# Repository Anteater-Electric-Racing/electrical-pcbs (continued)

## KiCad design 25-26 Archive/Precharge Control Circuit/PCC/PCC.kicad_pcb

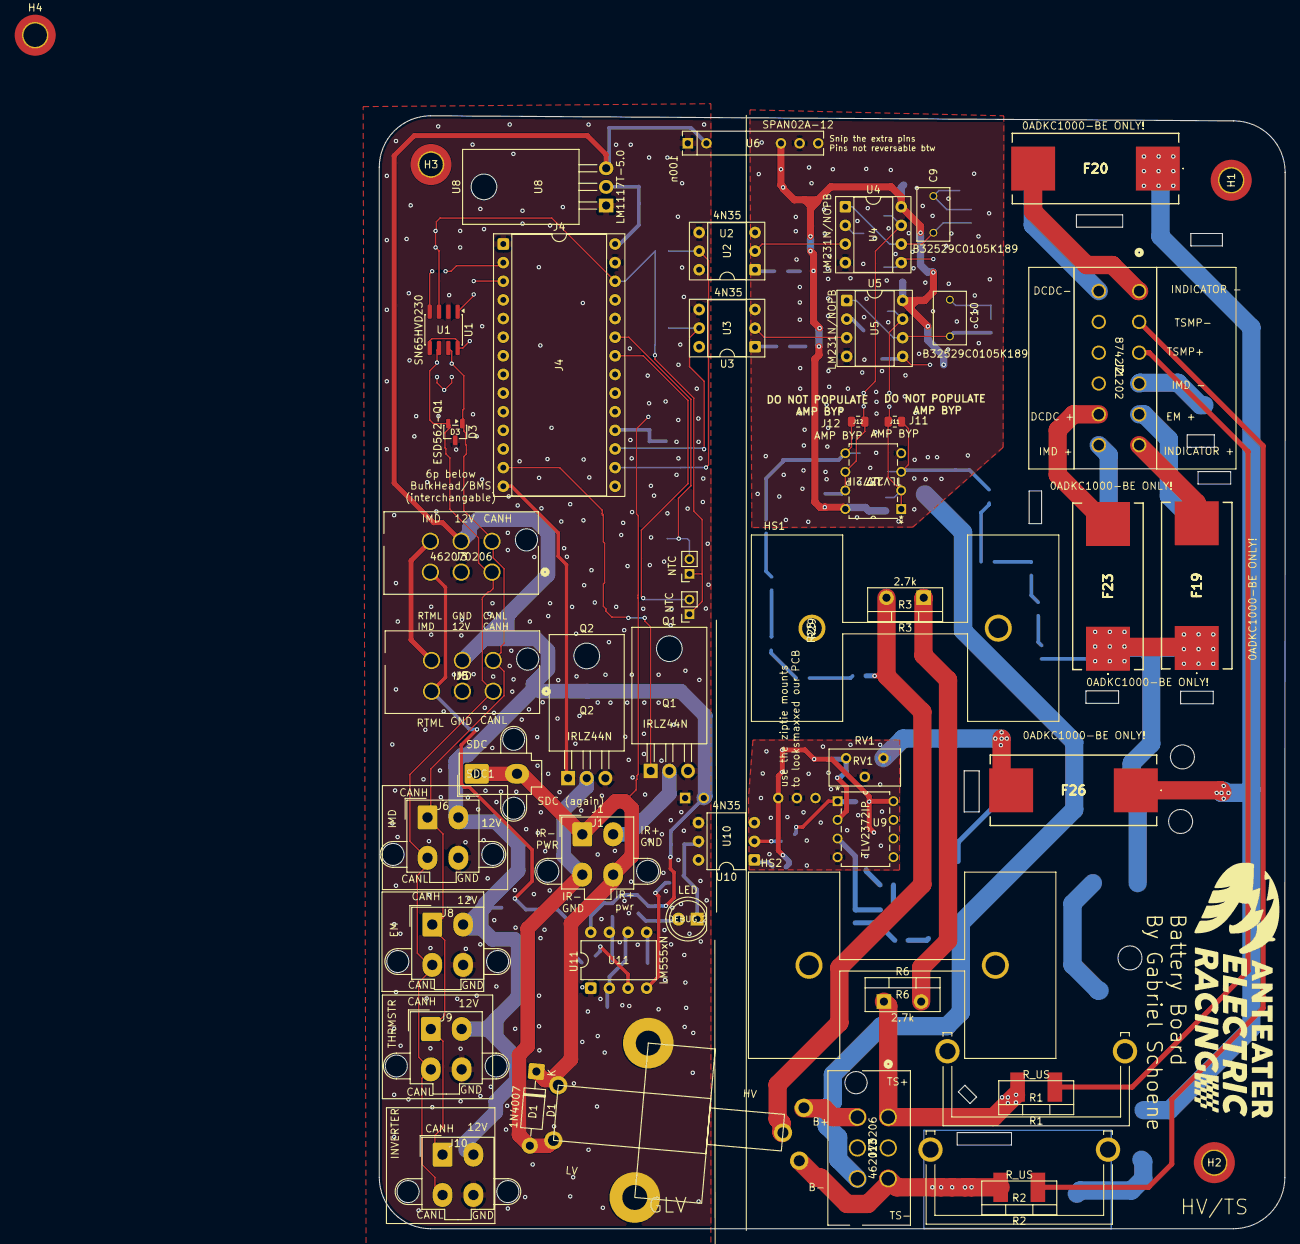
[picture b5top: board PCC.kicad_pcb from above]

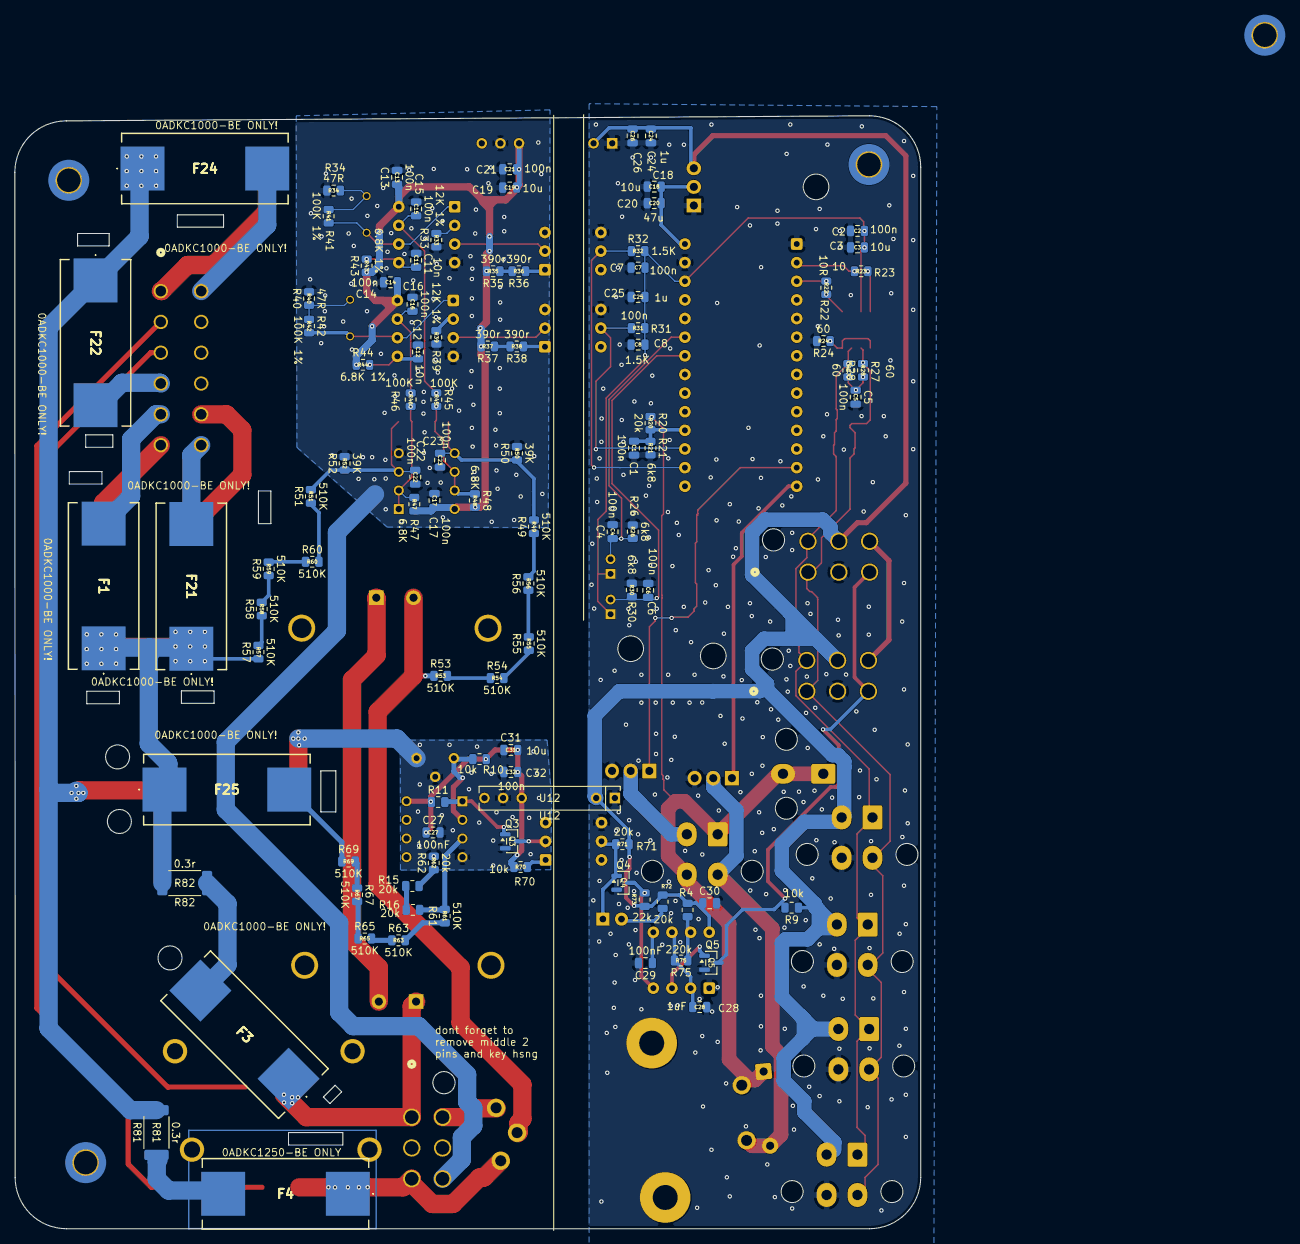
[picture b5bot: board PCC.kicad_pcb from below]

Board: 2 copper layers, 123.5 x 151.7 mm, 150 parts (99 on the bottom side), 93 nets.

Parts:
C1, C2, C4, C5, C6, C7, C8, C13, C14, C15, C16, C17, C21, C22, C23, C26, C32: 100n; C_0805_2012Metric
C3, C18, C19, C31: 10u; C_0805_2012Metric
C9, C10: B32529C0105K189; CAPRR500W50L730T450H950
C11, C12: 10n; C_0805_2012Metric
C20: 47u; C_0805_2012Metric
C24, C25: 1u; C_0805_2012Metric
C27, C29, C30: 100nF; C_0805_2012Metric
C28: 1uF; C_0805_2012Metric
D1: 1N4007; D_DO-41_SOD81_P10.16mm_Horizontal
D3: ESD562-Q1; SOT-23-3
DEBUG_2: LED; LED_D5.0mm
F1, F19, F20, F21, F22, F23, F24, F25, F26: 1A; 5x20fuseblock
F3, F4: 1.25; 5x20fuseblock
H1, H2, H3, H4: MountingHole_Pad; MountingHole_3.2mm_M3_DIN965_Pad_TopBottom
HS1, HS2: Heatsink_Pad; heatsink
HS3, HS4: Heatsink_Pad; smolsink
J1: Conn_01x04_Socket; Molex_Mini-Fit_Jr_5566-04A2_2x02_P4.20mm_Vertical
J2: 874271202; 12pSTminifit
J3, J13: 462070206; 6pMinifitJR
J4: Conn_02x14_Counter_Clockwise; DIP-28_W15.24mm_Socket
J5: IMD; 6pMinifitJR
J6: Thermistor Expansion; Molex_Mini-Fit_Jr_5566-04A2_2x02_P4.20mm_Vertical
J8: BMS; Molex_Mini-Fit_Jr_5566-04A2_2x02_P4.20mm_Vertical
J9: EnergyMeter; Molex_Mini-Fit_Jr_5566-04A2_2x02_P4.20mm_Vertical
J10: INVTR; Molex_Mini-Fit_Jr_5566-04A2_2x02_P4.20mm_Vertical
J11, J12: AMP BYP; R_0805_2012Metric
K1: Relay_SPDT; RH3_Mount
Q1, Q2: IRLZ44N; TO-220-3_Horizontal_TabDown
Q3, Q4, Q5: Q_NMOS_GSD; SOT-23
R1, R2: R_US; TO-220-2_Vertical-SMD
R3, R6: 2.7k; TO-220-2_Vertical
R4, R73: 22k; R_0805_2012Metric
R9, R10, R11, R70: 10k; R_0805_2012Metric
R15, R16, R20, R62, R71, R72: 20k; R_0805_2012Metric
R21, R26, R30: 6k8; R_0805_2012Metric
R22: 10R; R_0805_2012Metric
R23: 10; R_0805_2012Metric
R24, R27, R28: 60; R_0805_2012Metric
R25, R29: NTC; PinSocket_1x02_P2.00mm_Vertical
R31, R32: 1.5K; R_0805_2012Metric
R33, R39: 12K 1%; R_0805_2012Metric
R34, R40: 47R; R_0805_2012Metric
R35, R36, R37, R38: 390r; R_0805_2012Metric
R41, R42: 100K 1%; R_0805_2012Metric
R43, R44: 6.8K 1%; R_0805_2012Metric
R45, R46: 100K; R_0805_2012Metric
R47, R48: 6.8K; R_0805_2012Metric
R49, R51, R53, R54, R55, R56, R57, R58, R59, R60, R61, R63, R65, R67, R69: 510K; R_0805_2012Metric
R50, R52: 39K; R_0805_2012Metric
R75: 220k; R_0805_2012Metric
R81, R82: 0.3r; R_2512_6332Metric_Pad1.40x3.35mm_HandSolder
RV1: 1k default (1-5k); Potentiometer_Bourns_3296Y_Vertical
SDC1: Conn_01x02_Socket; Molex_Mini-Fit_Jr_5566-02A2_2x01_P4.20mm_Vertical
U1: SN65HVD230; SOIC-8_3.9x4.9mm_P1.27mm
U2, U3: 4N35; DIP-6_W7.62mm_Socket
U4, U5: DIP-8_W7.62mm_Socket
U6, U12: isoDCDC(removedPins)
U7, U9: TLV2372IP; P8
U8: LM1117T-5.0; TO-220-3_Horizontal_TabDown
U10: 4N35; DIP-6_W7.62mm
U11: LM555xN; DIP-8_W7.62mm

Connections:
12V_UNISO: C27.1, C31.2, C32.2, R10.1, R11.1, R70.1, U9.8 (VDD), U12.6 (+Vout)
+3.3V: C2.1, C3.1, C7.1, C8.1, C25.1, J4.26, R25.1, R29.1, R31.2, R32.2, U1.3 (VCC)
+5V: C18.1, C20.1, J4.28, U8.2 (VO)
+12 ISO: C13.1, C14.1, C17.1, C19.2, C21.2, R35.2, R37.2, R43.1, R44.1, R47.2, R48.2, U4.8 (VS), U5.8 (VS), U6.6 (+Vout), U7.8 (VDD)
/FusedTS + (IMD): F21.2, J2.12
/FusedTS + (expansion): F23.2, J2.11
/FusedTS + (indicator): F19.2, J2.6
/FusedTS - (IMD): F22.2, J2.4
/FusedTS - (expansion): F24.2, J2.7
/FusedTS - (indicator): F20.2, J2.1
/FusedTS+ (EM): F1.2, J2.5
/NTC 1: C4.1, J4.23, R25.2, R26.1
/NTC 2: C6.1, J4.22, R29.2, R30.1
/SDN signal: C1.1, J4.18, R20.2, R21.1
/TSMP+: J2.3, R1.1
/TSMP-: J2.2, R2.1
B+_in: J13.4, K1.14
CANH: D3.1 (K), J3.4, J5.4, J6.1, J8.1, J9.1, J10.1, R27.1, U1.7 (CANH)
CANL: D3.2 (K), J3.1, J5.1, J6.3, J8.3, J9.3, J10.3, R28.2, U1.6 (CANL)
CANRX: J4.2, R23.1
CANTX: J4.3, R22.2
Freq_Accumulator: J4.16, R32.1, U2.5
Freq_TS: J4.17, R31.1, U3.5
GLV+: C24.1, C26.1, C30.1, J3.5, J5.5, J6.2, J8.2, J9.2, J10.2, R4.1, R9.1, R71.1, R72.1, R73.1, U6.2 (+Vin), U8.3 (VI), U11.8 (VCC), U12.2 (+Vin)
GLV-: C1.2, C2.2, C3.2, C4.2, C5.2, C6.2, C7.2, C8.2, C18.2, C20.2, C24.2, C25.2, C26.2, C28.2, C29.2, C30.2, D3.3 (A), J3.2, J4.1, J4.27, J5.2, J6.4, J8.4, J9.4, J10.4, Q1.3 (S), Q2.3 (S), Q4.2 (S), Q5.2 (S), R21.2, R24.2, R26.2, R30.2, U1.2 (GND), U2.4, U3.4, U6.1 (-Vin), U8.1 (GND), U10.4, U11.1 (GND), U12.1 (-Vin)
GND ISO: C11.2, C12.2, C13.2, C14.2, C15.2, C16.2, C17.2, C19.1, C21.1, C22.2, C23.2, J13.6, R33.1, R34.2, R39.1, R40.2, R50.2, R52.2, U4.4 (GND), U5.4 (GND), U6.7 (-Vout), U7.4 (GND)
HighVoltage+: F25.2, R69.1
HighVoltage-: C27.2, C31.1, C32.1, F26.2, Q3.2 (S), R62.2, RV1.1, RV1.2, U9.4 (GND), U12.7 (-Vout)
IMD_Fault: J3.6, J5.6
IR+ CTRL: J4.13, Q1.1 (G)
IR+_GND: J1.2, Q1.2 (D)
IR-_GND: D1.2 (A), J1.3, K1.A2, Q2.2 (D)
unnamed: C5.1, R27.2, R28.1
unnamed: C9.1, R34.1, R41.1
unnamed: C10.1, R40.1, R42.1
unnamed: DEBUG_2.2 (A), R72.2
unnamed: DEBUG_2.1 (K), Q4.1 (G), R71.2, U10.5
unnamed: F3.2, R82.1
unnamed: F4.2, R81.1
unnamed: Q3.3 (D), U10.2
unnamed: Q3.1 (G), R11.2, U9.1 (1OUT)
unnamed: Q4.3 (D), R73.2, U11.4 (R)
unnamed: Q5.1 (G), U11.3 (Q)
unnamed: R3.1, R6.2
unnamed: R15.1, R16.2
unnamed: R15.2, R62.1
unnamed: R35.1, R36.2
unnamed: R36.1, U2.1
unnamed: R37.1, R38.2
unnamed: R38.1, U3.1
unnamed: R49.1, R56.2
unnamed: R51.1, R60.2
unnamed: R53.2, R54.1
unnamed: R54.2, R55.1
unnamed: R55.2, R56.1
unnamed: R57.2, R58.1
unnamed: R58.2, R59.1
unnamed: R59.2, R60.1
unnamed: R61.1, R63.2
unnamed: R63.1, R65.2
unnamed: R65.1, R67.2
unnamed: R67.1, R69.2
unnamed: R70.2, U10.1
unnamed: R22.1, U1.1 (D)
unnamed: R23.2, U1.4 (R)
unnamed: R24.1, U1.5 (Vref), U1.8 (Rs)
unnamed: C15.1, R45.1, U4.7 (COMPIN)
unnamed: U2.2, U4.3 (FOUT)
unnamed: C9.2, R41.2, U4.1 (IOUT), U4.6 (THRESH)
unnamed: R33.2, U4.2 (IREF)
unnamed: C11.1, R43.2, U4.5 (RC)
unnamed: C16.1, R46.1, U5.7 (COMPIN)
unnamed: U3.2, U5.3 (FOUT)
unnamed: C10.2, R42.2, U5.1 (IOUT), U5.6 (THRESH)
unnamed: R39.2, U5.2 (IREF)
unnamed: C12.1, R44.2, U5.5 (RC)
unnamed: C22.1, J11.2, R51.2, R52.1, U7.3 (1IN+)
unnamed: J11.1, R46.2, R47.1, U7.1 (1OUT), U7.2 (1IN-)
unnamed: C23.1, J12.2, R49.2, R50.1, U7.5 (2IN+)
unnamed: J12.1, R45.2, R48.1, U7.6 (2IN-), U7.7 (2OUT)
unnamed: C29.1, U11.5 (CV)
unnamed: R4.2, R75.1, U11.7 (DIS)
unnamed: C28.1, R75.2, U11.2 (TR), U11.6 (THR)
PreDis_IR-: J4.14, Q2.1 (G)
RTM_SIG: J3.3, J5.3, Q5.3 (D), R9.2
Shutdown_in: D1.1 (K), J1.1, J1.4, K1.A1, R20.1, SDC1.1, SDC1.2
TS+: F1.1, F19.1, F21.1, F23.1, F25.1, R57.1, R82.2
TS+ unfused: F3.1, J13.1, R1.2, R6.1
TS-: F20.1, F22.1, F24.1, F26.1, R81.2
TS- unfused: F4.1, J13.3, K1.12, R2.2
V_BIAS: R10.2, RV1.3, U9.2 (1IN-)
V_SNS: R16.1, R61.2, U9.3 (1IN+)
Vin_Accu: K1.11, R3.2, R53.1

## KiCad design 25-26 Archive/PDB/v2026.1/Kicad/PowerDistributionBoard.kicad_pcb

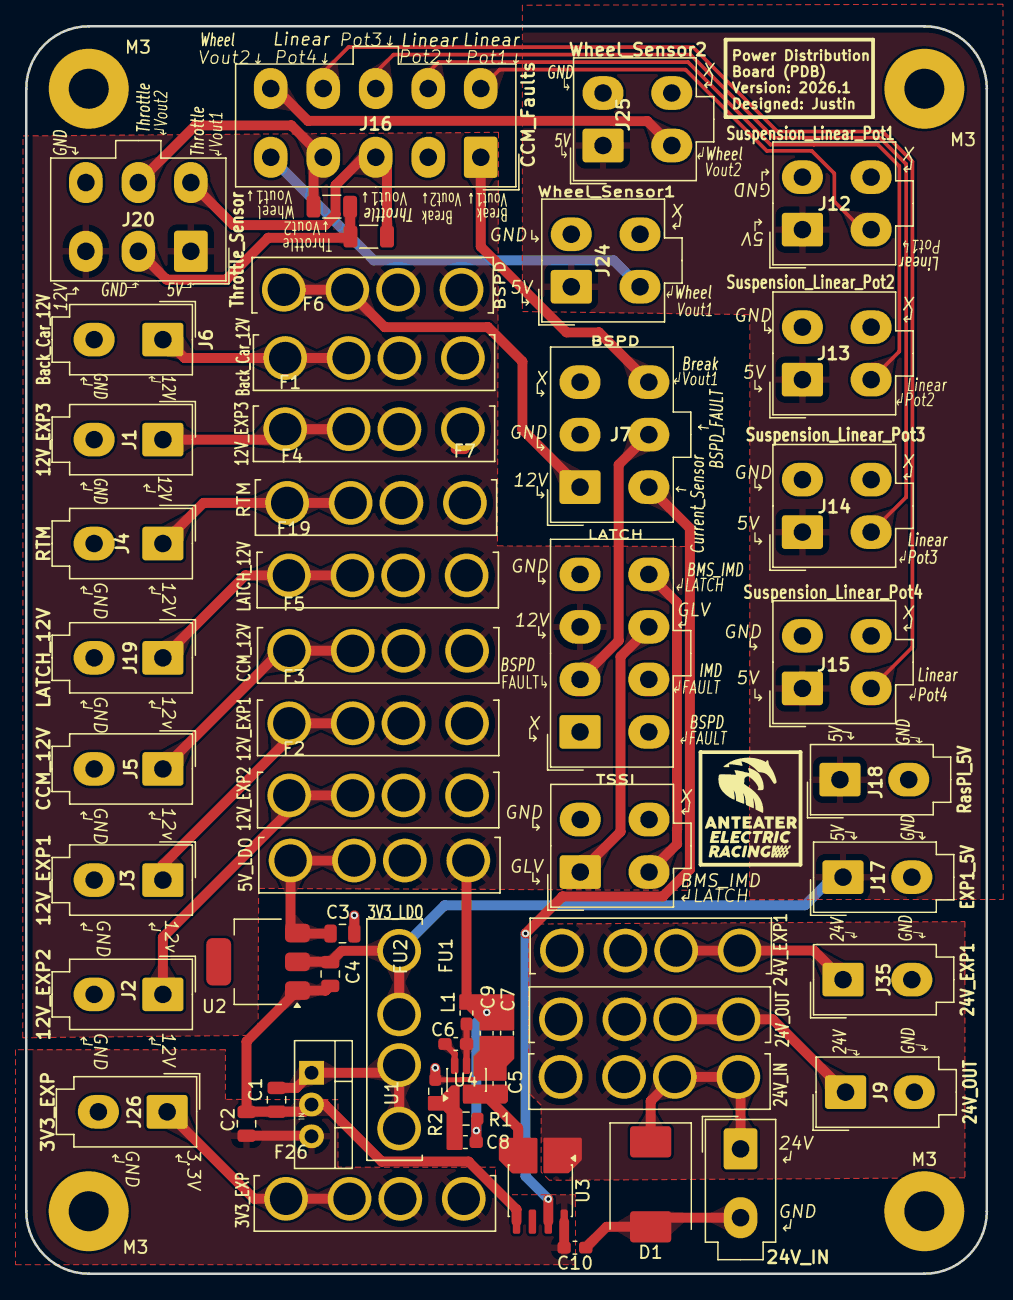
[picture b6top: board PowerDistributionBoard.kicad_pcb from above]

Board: 2 copper layers, 76.8 x 99.8 mm, 62 parts (0 on the bottom side), 36 nets.

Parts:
C1: 0.47uF; C_0805_2012Metric
C2: 33uF; C_0805_2012Metric
C3: 1uF; C_0805_2012Metric
C4: 2.2uF; C_0805_2012Metric
C5: 10uF; C_0603_1608Metric_Pad1.08x0.95mm_HandSolder
C6, C10: 100nF; C_0603_1608Metric_Pad1.08x0.95mm_HandSolder
C7, C9: 22uF; C_0603_1608Metric_Pad1.08x0.95mm_HandSolder
C8: 56pF; C_0603_1608Metric_Pad1.08x0.95mm_HandSolder
D1: 1.5SMCxxA; D_SMC
F1: 12V_EXP3; FUSE_3522-2
F2: 12V_EXP2; FUSE_3522-2
F3: 12V_EXP1; FUSE_3522-2
F4: RTM; FUSE_3522-2
F5: CCM_12V; FUSE_3522-2
F6: Back_Car_12V; FUSE_3522-2
F7: BSPD; FUSE_3522-2
F8: 24V_OUT; FUSE_3522-2
F9: 24V_IN; FUSE_3522-2
F19: LATCH_12V; FUSE_3522-2
F26: 3V3_EXP; FUSE_3522-2
F35: 24V_EXP1; FUSE_3522-2
FU1: 3V3_LDO; FUSE_3522-2
FU2: 5V_LDO; FUSE_3522-2
J1: 12V_EXP3; Molex_Mini-Fit_Jr_5566-02A_2x01_P4.20mm_Vertical
J2: 12V_EXP2; Molex_Mini-Fit_Jr_5566-02A_2x01_P4.20mm_Vertical
J3: 12V_EXP1; Molex_Mini-Fit_Jr_5566-02A_2x01_P4.20mm_Vertical
J4: RTM; Molex_Mini-Fit_Jr_5566-02A_2x01_P4.20mm_Vertical
J5: CCM_12V; Molex_Mini-Fit_Jr_5566-02A_2x01_P4.20mm_Vertical
J6: Back_Car_12V; Molex_Mini-Fit_Jr_5566-02A_2x01_P4.20mm_Vertical
J7: BSPD; Molex_Mini-Fit_Jr_5566-06A_2x03_P4.20mm_Vertical
J8: TSSI; Molex_Mini-Fit_Jr_5566-04A_2x02_P4.20mm_Vertical
J9: 24V_OUT; Molex_Mini-Fit_Jr_5566-02A_2x01_P4.20mm_Vertical
J10: 24V_IN; Molex_Mini-Fit_Jr_5566-02A_2x01_P4.20mm_Vertical
J11: LATCH; Molex_Mini-Fit_Jr_5566-08A_2x04_P4.20mm_Vertical
J12: Suspension_Linear_Pot1; Molex_Mini-Fit_Jr_5566-04A_2x02_P4.20mm_Vertical
J13: Suspension_Linear_Pot2; Molex_Mini-Fit_Jr_5566-04A_2x02_P4.20mm_Vertical
J14: Suspension_Linear_Pot3; Molex_Mini-Fit_Jr_5566-04A_2x02_P4.20mm_Vertical
J15: Suspension_Linear_Pot4; Molex_Mini-Fit_Jr_5566-04A_2x02_P4.20mm_Vertical
J16: CCM_Faults; Molex_Mini-Fit_Jr_5566-10A_2x05_P4.20mm_Vertical
J17: EXP1_5V; Molex_Mini-Fit_Jr_5566-02A_2x01_P4.20mm_Vertical
J18: RasPI_5V; Molex_Mini-Fit_Jr_5566-02A_2x01_P4.20mm_Vertical
J19: LATCH_12V; Molex_Mini-Fit_Jr_5566-02A_2x01_P4.20mm_Vertical
J20: Throttle_Sensor; Molex_Mini-Fit_Jr_5566-06A_2x03_P4.20mm_Vertical
J24: Wheel_Sensor1; Molex_Mini-Fit_Jr_5566-04A_2x02_P4.20mm_Vertical
J25: Wheel_Sensor2; Molex_Mini-Fit_Jr_5566-04A_2x02_P4.20mm_Vertical
J26: 3V3_EXP; Molex_Mini-Fit_Jr_5566-02A_2x01_P4.20mm_Vertical
J35: 24V_EXP1; Molex_Mini-Fit_Jr_5566-02A_2x01_P4.20mm_Vertical
L1: 10uH; L_0603_1608Metric_Pad1.05x0.95mm_HandSolder
M3, M3#2, M3#3, M3#4: MountingHole M3; MountingHole_3.2mm_M3_Pad
R1: 249k; R_0603_1608Metric_Pad0.98x0.95mm_HandSolder
R2: 18k; R_0603_1608Metric_Pad0.98x0.95mm_HandSolder
R3, R4: 10K; R_1206_3216Metric
U1: 5to3.3_Linear_Regulator; TO-220-3_Vertical
U2: TLV76150DCYR; SOT-223
U3: ACS711xLCTR-12AB; SOIC-8_3.9x4.9mm_P1.27mm
U4: AP63200WU; TSOT-23-6

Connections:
3.3V: C2.1, C10.2, F26.2, U1.3 (VO), U3.8 (VCC)
5V: C4.1, FU1.1, J12.1, J13.1, J14.1, J15.1, J17.1, J18.1, J24.1, J25.1, U2.2 (OUT)
12V: C7.1, C8.1, C9.1, F1.2, F2.2, F3.2, F4.2, F5.2, F6.2, F7.1, F19.2, FU2.2, J11.3, J20.1, J20.3, L1.2, R1.1
24V: F8.2, F9.1, F35.2, U3.1 (IP+), U3.2 (IP+)
/BST: C6.2, U4.6 (BST)
/BUCK_IN: C5.1, U3.3 (IP-), U3.4 (IP-), U4.2 (EN), U4.3 (IN)
/Back_Car_12V: F6.1, J6.1
/FB: C8.2, R1.2, R2.1, U4.1 (FB)
/Fuse_5to3.3: C1.1, FU1.2, U1.1 (VI)
/Fuse_12to5: C3.1, FU2.1, U2.3 (IN)
/Fuse_24V_OUT: F8.1, J9.1
/Fuse_BSPD: F7.2, J7.1
/Fuse_CCM_12V: F5.1, J5.1
/Fuse_EXP1_12V: F3.1, J3.1
/Fuse_EXP1_24V: F35.1, J35.1
/Fuse_EXP2_12V: F2.1, J2.1
/Fuse_EXP3_12V: F1.1, J1.1
/Fuse_EXP_3V3: F26.1, J26.1
/Fuse_LATCH_12V: F19.1, J19.1
/Fuse_RTM: F4.1, J4.1
/SW: C6.1, L1.1, U4.5 (SW)
BSPD_FAULT: J7.5, J11.2
Brake_Sensor_Vout1: J7.6, J16.1
Current_Sensor: J7.4, U3.7 (VIOUT)
GLV: J8.1, J11.7
GND: C1.2, C2.2, C3.2, C4.2, C5.2, C7.2, C9.2, C10.1, D1.2 (A2), J1.2, J2.2, J3.2, J4.2, J5.2, J6.2, J7.2, J8.2, J9.2, J10.2, J11.4, J12.2, J13.2, J14.2, J15.2, J17.2, J18.2, J19.2, J20.2, J20.6, J24.2, J25.2, J26.2, J35.2, R2.2, R3.2, R4.2, U1.2 (GND), U2.1 (GND), U3.5 (GND), U4.4 (GND)
Linear_Pot1: J12.3, J16.6
Linear_Pot2: J13.3, J16.7
Linear_Pot3: J14.3, J16.8
Linear_Pot4: J15.3, J16.9
unnamed: D1.1 (A1), F9.2, J10.1
Throttle_Sensor_Vout1: J16.3, J20.4, R3.1
Throttle_Sensor_Vout2: J16.4, J20.5, R4.1
Wheel_Sensor_Vout1: J16.5, J24.3
Wheel_Sensor_Vout2: J16.10, J25.3
bms_imd_latch_only: J8.3, J11.8

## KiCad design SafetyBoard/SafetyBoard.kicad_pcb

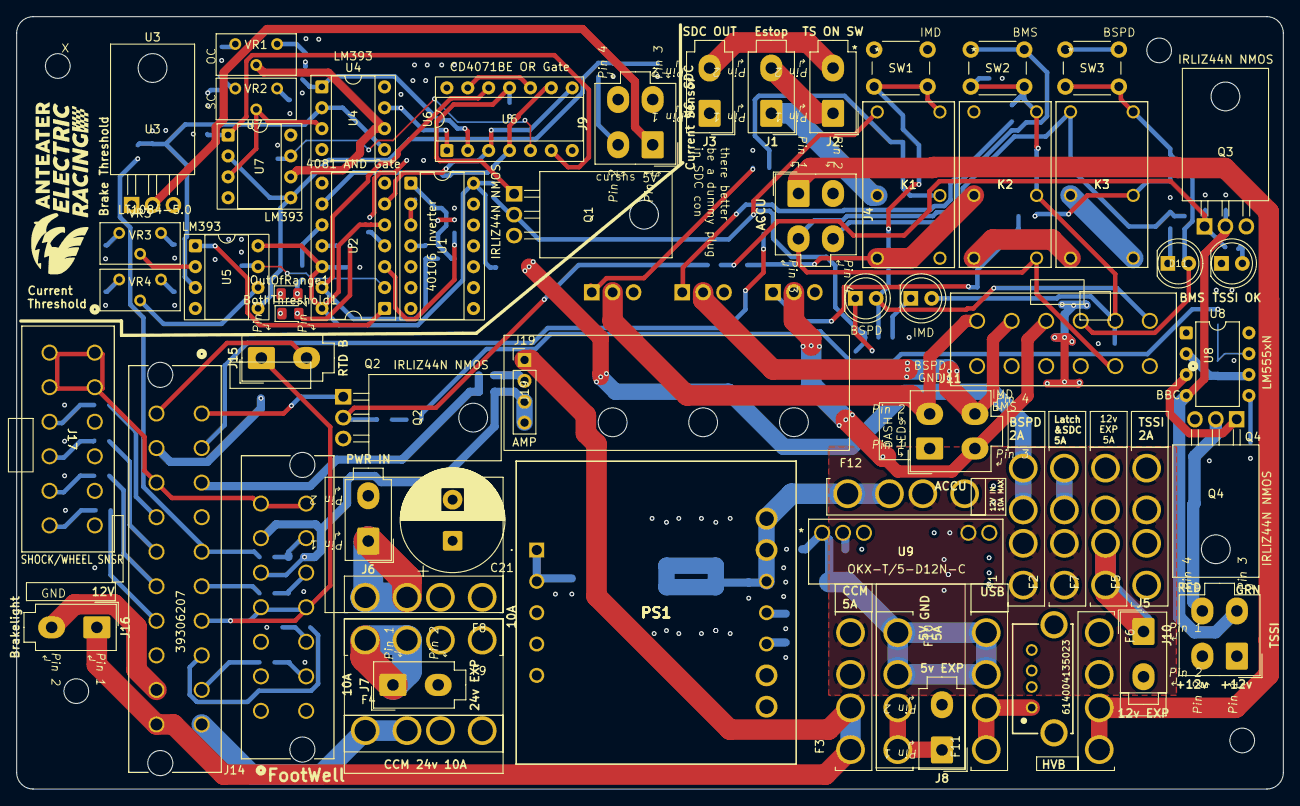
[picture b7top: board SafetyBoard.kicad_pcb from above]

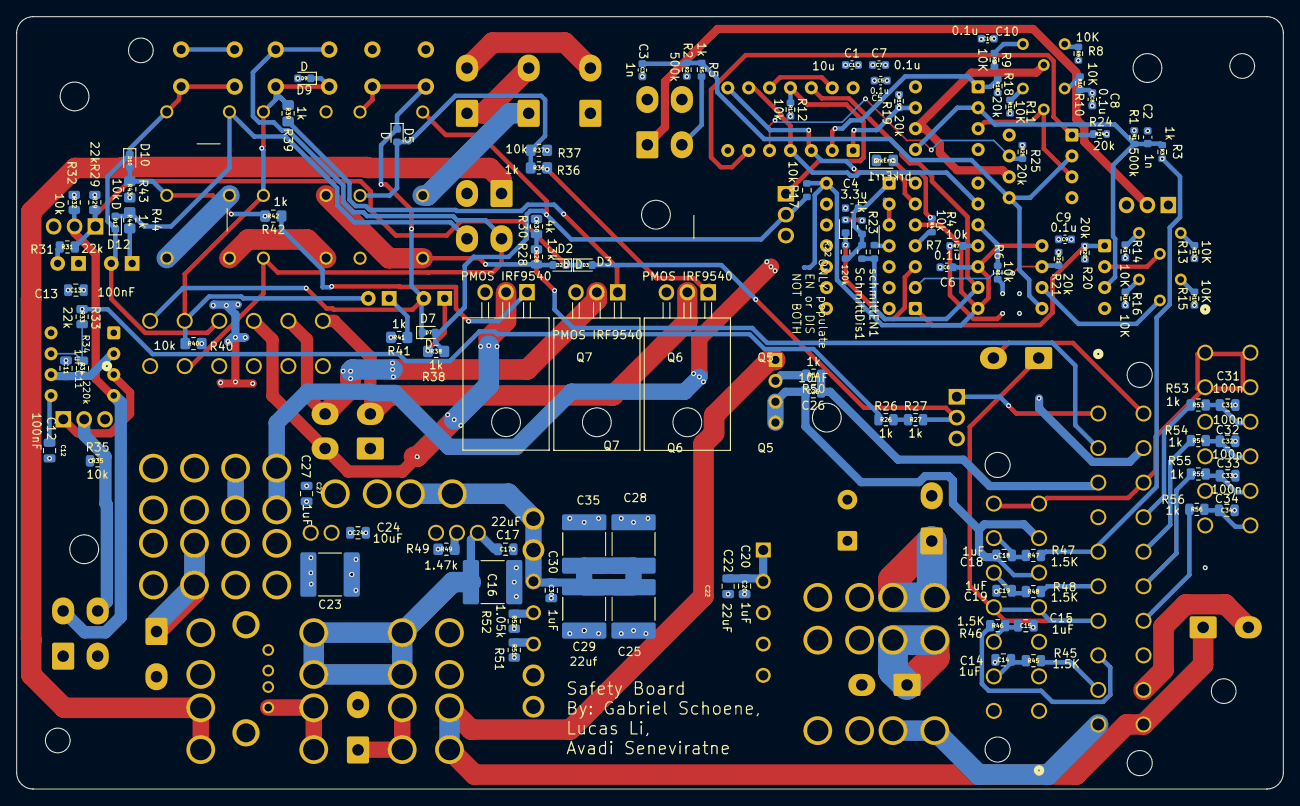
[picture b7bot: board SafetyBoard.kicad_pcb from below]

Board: 4 copper layers, 154.0 x 93.9 mm, 170 parts (104 on the bottom side), 113 nets.

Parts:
BothThreshold1: APTD2012LSYCK; LED_0805_2012Metric_Pad1.15x1.40mm_HandSolder
C1: 10u; C_0603_1608Metric
C2, C3: 1n; C_0603_1608Metric
C4: 3.3u; C_0603_1608Metric
C5, C6, C7, C8, C9, C10: 0.1u; C_0603_1608Metric
C11, C14, C15, C18, C19, C20, C27, C30: 1uF; C_0805_2012Metric
C12, C13: 100nF; C_0805_2012Metric
C16, C23, C25, C28, C29, C35: 22uf; C_2220_5750Metric_Pad1.97x5.40mm_HandSolder
C17, C22: 22uF; C_0805_2012Metric
C21: 330uF; CP_Radial_D12.5mm_P5.00mm
C24: 10uF; C_0805_2012Metric
C26: 10nF; C_0805_2012Metric
C31, C32, C33, C34: 100n; C_0805_2012Metric
D1, D2, D3, D5, D7, D9, D10, D12: D; D_0603_1608Metric
D4: ON when ok; LED_D5.0mm
D6, D8, D11: DEBUG LED; LED_D5.0mm
F1, F5: 2A MAX; FUSE_3522-2
F2, F3, F6, F7, F10: 5A MAX; FUSE_3522-2
F4, F8, F9: 10A MAX; FUSE_3522-2
F11: 3A MAX; FUSE_3522-2
F12: FUSE_3522-2
H1, H2, H3, H4: MH; MountingHole_3mm
J1: Estop; Molex_Mini-Fit_Jr_5566-02A_2x01_P4.20mm_Vertical
J2: TS ON SW; Molex_Mini-Fit_Jr_5566-02A_2x01_P4.20mm_Vertical
J3: SDC OUT; Molex_Mini-Fit_Jr_5566-02A_2x01_P4.20mm_Vertical
J4, J11: ACCU; Molex_Mini-Fit_Jr_5566-04A_2x02_P4.20mm_Vertical
J5: 12v EXP; Molex_Mini-Fit_Jr_5566-02A_2x01_P4.20mm_Vertical
J6: PWR IN; Molex_Mini-Fit_Jr_5566-02A_2x01_P4.20mm_Vertical
J7: 24v EXP; Molex_Mini-Fit_Jr_5566-02A_2x01_P4.20mm_Vertical
J8: 5v EXP; Molex_Mini-Fit_Jr_5566-02A_2x01_P4.20mm_Vertical
J9: Current Sensor; Molex_Mini-Fit_Jr_5566-04A_2x02_P4.20mm_Vertical
J10: TSSI; Molex_Mini-Fit_Jr_5566-04A_2x02_P4.20mm_Vertical
J12: BBC; 12pSTminifit
J13: 614004135023
J14: footwell; 14pSTminifit
J15: RTD B; Molex_Mini-Fit_Jr_5566-02A_2x01_P4.20mm_Vertical
J16: Brakelight; Molex_Mini-Fit_Jr_5566-02A_2x01_P4.20mm_Vertical
J17: SHOCK/WHEEL SNSR; 12pSTminifit
J18: 39306207; 20pSTminfit
J19: AMP; AmpBoard
K1, K2, K3: G6B-2214P-US DC12; DPSTrelay
OutOfRange1: APTD2012LSYCK; LED_0805_2012Metric_Pad1.15x1.40mm_HandSolder
PS1: I7A24080A033V-0C3-R; 24V DCDC I7A24080A033V0C3R
Q1, Q2, Q3, Q4: IRLIZ44N NMOS; TO-220F-3_Horizontal_TabDown
Q5, Q6, Q7: PMOS IRF9540; TO-220F-3_Horizontal_TabDown
R1, R2: 500k; R_0603_1608Metric
R3, R5, R23: 1k; R_0603_1608Metric
R4, R6, R7, R12, R17: 10k; R_0603_1608Metric
R8, R9, R10, R11, R13, R14, R15, R16: 10K; R_0603_1608Metric
R18, R19, R20, R21, R24, R25: 20k; R_0603_1608Metric
R22: 120k; R_0603_1608Metric
R26, R27, R50, R53, R54, R55, R56: 1k; R_0805_2012Metric
R28: 13k; R_0805_2012Metric
R29, R31, R33: 22k; R_0805_2012Metric
R30: 4k; R_0805_2012Metric
R32, R35: 10k; R_0805_2012Metric
R34: 220k; R_0805_2012Metric
R36, R38, R39, R41, R42, R44: 1k; R_0805_2012Metric_Pad1.20x1.40mm_HandSolder
R37, R40, R43: 10k; R_0805_2012Metric_Pad1.20x1.40mm_HandSolder
R45, R46, R47, R48: 1.5K; R_0805_2012Metric
R49: 1.47k; R_0805_2012Metric_Pad1.20x1.40mm_HandSolder
R51: R_0805_2012Metric
R52: 1.05k; R_0805_2012Metric
SW1, SW2, SW3: SW_Push; SW_PUSH_6mm
SchmittDis1: 0; R_0603_1608Metric
U1: 40106 Inverter; DIP-14_W7.62mm_Socket
U2: 4081 AND Gate; DIP-14_W7.62mm_Socket
U3: LT1084-5.0; TO-220-3_Horizontal_TabDown
U4, U5, U7: LM393; DIP-8_W7.62mm_Socket
U6: CD4071BE OR Gate; DIP-14_W7.62mm_Socket
U8: LM555xN; DIP-8_W7.62mm
U9: OKX-T/5-D12N-C; 12v5vDCDC
VR1, VR2, VR3, VR4: 3296Y-11-103LF; Potentiometer_Bourns_3296Y_Vertical
brkErr1: APTD2012LSYCK; LED_0805_2012Metric_Pad1.15x1.40mm_HandSolder
schmittEN1: 0; R_0603_1608Metric

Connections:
+5V: J9.1, U3.2 (VO)
+12V: C1.1, C5.1, C6.1, C7.1, C8.1, C9.1, C10.1, F1.2, F2.2, J12.1, J12.3, K1.5, K3.3, K3.5, Q5.3 (S), Q6.3 (S), Q7.3 (S), R8.1, R10.1, R13.1, R15.1, R17.1, R18.2, R19.2, R20.2, R21.2, R24.2, R25.2, SW1.1, SW3.1, U1.14 (VDD), U2.5, U2.8, U2.12, U2.14 (VDD), U3.3 (VI), U4.8 (V+), U5.8 (V+), U6.14 (VDD), U7.8 (V+)
/5V: C16.1, C17.1, F10.1, F11.2, U9.1 (+VOUT)
/12V: C23.1, C24.1, C27.1, F1.1, F2.1, F3.2, F5.2, F6.1, F7.2, F12.2, U9.4 (+VIN)
/24V: C20.1, C21.1, C22.1, F4.2, F8.1, F9.1, PS1.1 (VIN_(+)_1), PS1.9 (VIN_(+)_2)
/BMS FAULT: D12.2 (A), J4.4, K3.1, R44.2
/BSPD/BOTH_ON: SchmittDis1.2, U2.13, U6.12, schmittEN1.1
/BSPD/BRAKE: C2.1, R1.2, R3.1, U4.2 (-), U4.5 (+), U5.3 (+)
/BSPD/BRAKE_APPLIED: R20.1, U2.1, U5.1
/BSPD/BRAKE_ERROR: U2.6, U6.3, U6.8
/BSPD/BRAKE_OPEN: R19.1, U4.7, U6.1
/BSPD/BRAKE_SHORT: R18.1, U4.1, U6.2
/BSPD/BRAKE_THRESHOLD: U5.2 (-), VR3.2 (WIPER)
/BSPD/BSPD_FAULT: D7.2 (A), K1.1, Q1.2 (D), R17.2, R38.2
/BSPD/B_IN: J18.5, R3.2, R47.2
/BSPD/CURRENT: C3.1, R2.2, R5.1, U5.5 (+), U7.2 (-), U7.5 (+)
/BSPD/C_IN: J9.2, R5.2
/BSPD/FAULT_SENSED: Q1.1 (G), R12.1, U6.11
/BSPD/OPEN_CIRCUIT: U4.6 (-), U7.6 (-), VR1.2 (WIPER)
/BSPD/PEDAL_APPLIED: R21.1, U2.2, U5.7
/BSPD/PEDAL_ERROR: U2.9, U6.4, U6.9
/BSPD/PEDAL_OPEN: R25.1, U6.5, U7.7
/BSPD/PEDAL_SHORT: R24.1, U6.6, U7.1
/BSPD/PEDAL_THRESHOLD: U5.6 (-), VR4.2 (WIPER)
/BSPD/SHORT_CIRCUIT: U4.3 (+), U7.3 (+), VR2.2 (WIPER)
/CCM Helper/5V: J14.7, J14.14, J17.1, J17.2, J17.7, J17.8, J18.13
/CCM Helper/12V: F3.1, J16.1, J18.20, J19.1
/CCM Helper/24V: F4.1, J18.10
/CCM Helper/APPS1 IN: C15.1, J14.10, R46.1
/CCM Helper/APPS1 OUT: J18.8, R46.2
/CCM Helper/APPS2 IN: C14.1, J14.9, R45.1
/CCM Helper/APPS2 OUT: J18.9, R45.2
/CCM Helper/BPS1 IN: C18.1, J14.13, R47.1
/CCM Helper/BPS2 IN: C19.1, J14.12, R48.1
/CCM Helper/BPS2 OUT: J18.6, R48.2
/CCM Helper/Brakelight: J16.2, J18.19
/CCM Helper/CCM3v3: J14.4, J14.11, J15.1, J18.7
/CCM Helper/CCM fdbk: J18.2, R28.2, R30.1
/CCM Helper/CCMGND: C14.2, C15.2, C18.2, C19.2, C26.2, C31.2, C32.2, C33.2, C34.2, J14.2, J14.3, J14.5, J14.6, J17.3, J17.4, J17.5, J17.6, J18.4, J19.3, J19.4
/CCM Helper/RTDB: J15.2, J18.11
/CCM Helper/Speaker IN: C26.1, J18.3, R50.1
/CCM Helper/Speaker LPF'd: J19.2, R50.2
/CCM Helper/TSSI BYP: J18.1, Q2.1 (G)
/CCM Helper/Wheel/Shock1 IN: C31.1, J17.9, R53.2
/CCM Helper/Wheel/Shock1 OUT: J18.14, R53.1
/CCM Helper/Wheel/Shock2 IN: C32.1, J17.10, R54.2
/CCM Helper/Wheel/Shock2 OUT: J18.15, R54.1
/CCM Helper/Wheel/Shock3 IN: C33.1, J17.11, R55.2
/CCM Helper/Wheel/Shock3 OUT: J18.16, R55.1
/CCM Helper/Wheel/Shock4 IN: C34.1, J17.12, R56.2
/CCM Helper/Wheel/Shock4 OUT: J18.17, R56.1
/IMD Fault: J4.3, J12.2, K2.5, SW2.1
/LATCH/BMSfault_LED: J11.3, J12.10, Q7.2 (D)
/LATCH/BSPDfault_LED: J11.2, J12.12, Q5.2 (D)
/LATCH/GVLM_OUTPUT: J1.1, K1.3
/LATCH/IMDfault_LED: J11.4, J12.11, Q6.2 (D)
/LATCH/bms_imd_latch_only: D2.2 (A), K1.4, K2.3, R28.1
/LATCH/bms_reset: D10.1 (K), D11.2 (A), D12.1 (K), J12.9, K3.8, SW3.2
/LATCH/bspd_reset: D5.1 (K), D6.2 (A), D7.1 (K), J12.7, K1.8, SW1.2
/LATCH/imd_reset: D8.2 (A), D9.1 (K), J12.8, K2.6, K2.8, R39.2, R40.1, SW2.2
/TSSI/GLV: C13.1, F5.1, J10.1, J10.2, R26.1, R32.1, R33.1, R35.1, U8.8 (VCC)
/TSSI/GREEN_LED: J10.3, Q3.2 (D), R32.2, U8.4 (R)
/TSSI/RED_LED: J10.4, Q4.2 (D), R35.2
GND: BothThreshold1.1 (K), C1.2, C2.2, C3.2, C4.2, C5.2, C6.2, C7.2, C8.2, C9.2, C10.2, C11.2, C12.2, C13.2, C16.2, C17.2, C20.2, C21.2, C22.2, C23.2, C24.2, C25.2, C27.2, C28.2, C29.2, C30.2, C35.2, D4.1 (K), D9.2 (A), J4.2, J5.2, J6.2, J7.2, J8.2, J9.4, J11.1, J12.4, J12.5, J12.6, J13.4 (GND), J13.S1, J13.S2, J18.12, K2.1, OutOfRange1.1 (K), PS1.2 (ON/OFF), PS1.3 (VIN_(-)_/_GND_1), PS1.4 (VOUT_(-)_/_GND_1), PS1.10 (VIN_(-)_/_GND_2), PS1.11 (VOUT_(-)_/_GND_2), Q1.3 (S), Q2.3 (S), Q3.3 (S), Q4.3 (S), R1.1, R2.1, R9.2, R11.2, R12.2, R14.2, R16.2, R29.2, R30.2, R37.2, R40.2, R41.2, R43.2, R49.2, R51.2, R52.2, U1.5, U1.7 (VSS), U1.9, U1.11, U1.13, U2.7 (VSS), U3.1 (GND), U4.4 (V-), U5.4 (V-), U6.7 (VSS), U7.4 (V-), U8.1 (GND), U9.3 (GND_COMMON), U9.5 (REMOTE_ON/OFF), brkErr1.1 (K)
unnamed: BothThreshold1.2 (A), R7.2
unnamed: C4.1, R22.2, R23.2, SchmittDis1.1, U1.1
unnamed: D1.2 (A), R23.1
unnamed: D1.1 (K), R22.1, U2.3
unnamed: D2.1 (K), D3.1 (K), Q3.1 (G), R29.1, R31.1
unnamed: D3.2 (A), Q2.2 (D), R27.2
unnamed: D4.2 (A), R31.2
unnamed: D5.2 (A), K1.6, R36.2, R37.1
unnamed: D6.1 (K), R38.1
unnamed: D8.1 (K), R41.1
unnamed: D10.2 (A), K3.6, R42.2, R43.1
unnamed: D11.1 (K), R44.1
unnamed: J1.2, J2.1
unnamed: J2.2, J3.2
unnamed: F6.2, J4.1
unnamed: F7.1, J5.1
unnamed: F8.2, J6.1
unnamed: F9.2, J7.1
unnamed: F10.2, J8.1
unnamed: F11.1, J13.1 (VBUS)
unnamed: K2.4, K3.4
unnamed: OutOfRange1.2 (A), R6.2
unnamed: PS1.5 (CURRENT_LIMIT_(OCP)_ADJUST), R51.1
unnamed: C25.1, C28.1, C29.1, C30.1, C35.1, F12.1, PS1.7 (SENSE+), PS1.8 (VOUT_(+)_1), PS1.12 (VOUT_(+)_2)
unnamed: PS1.6 (TRIM), R52.1
unnamed: Q4.1 (G), U8.3 (Q)
unnamed: Q5.1 (G), R36.1
unnamed: Q6.1 (G), R39.1
unnamed: Q7.1 (G), R42.1
unnamed: R4.1, U2.4
unnamed: R6.1, U2.10
unnamed: R7.1, U2.11
unnamed: R26.2, R27.1
unnamed: U1.2, U1.3
unnamed: U1.4, schmittEN1.2
unnamed: U6.10, U6.13
unnamed: C12.1, U8.5 (CV)
unnamed: R33.2, R34.1, U8.7 (DIS)
unnamed: C11.1, R34.2, U8.2 (TR), U8.6 (THR)
unnamed: R49.1, U9.2 (TRIM)
unnamed: R9.1, VR1.1 (CCW)
unnamed: R8.2, VR1.3 (CW)
unnamed: R11.1, VR2.1 (CCW)
unnamed: R10.2, VR2.3 (CW)
unnamed: R14.1, VR3.1 (CCW)
unnamed: R13.2, VR3.3 (CW)
unnamed: R16.1, VR4.1 (CCW)
unnamed: R15.2, VR4.3 (CW)
unnamed: R4.2, brkErr1.2 (A)

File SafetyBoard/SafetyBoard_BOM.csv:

"Reference","Qty","Value","DNP","Exclude from BOM","Exclude from Board","Footprint","MPN","MFG"
"R49","1","1.47k","","","","Resistor_SMD:R_0805_2012Metric_Pad1.20x1.40mm_HandSolder","RK73H2ATTD1471F ","KOA Speer Electronics, Inc. "
"R37,R40,R43","3","10k","","","","Resistor_SMD:R_0805_2012Metric_Pad1.20x1.40mm_HandSolder","RK73H2ATTD1002F","KOA Speer Electronics, Inc."
"R36,R38,R39,R41,R42,R44","6","1k","","","","Resistor_SMD:R_0805_2012Metric_Pad1.20x1.40mm_HandSolder","RK73H2ATTD1001F","KOA Speer Electronics, Inc."
"R52","1","1.05k","","","","Resistor_SMD:R_0805_2012Metric","RNCF0805DKE1K05","Stackpole Electronics Inc"
"R51","1","~","","","","Resistor_SMD:R_0805_2012Metric","",""
"R45,R46,R47,R48","4","1.5K","","","","Resistor_SMD:R_0805_2012Metric","ERJ-6GEYJ152V ","Panasonic Electronic Components "
"R34","1","220k","","","","Resistor_SMD:R_0805_2012Metric","RK73H2ATTD2203F","KOA Speer Electronics, Inc."
"R32,R35","2","10k","","","","Resistor_SMD:R_0805_2012Metric","RK73H2ATTD1002F","KOA Speer Electronics, Inc."
"R30","1","4k","","","","Resistor_SMD:R_0805_2012Metric","RK73H2ATTD4021F","KOA Speer Electronics, Inc."
"R29,R31,R33","3","22k","","","","Resistor_SMD:R_0805_2012Metric","RK73H2ATTD2202F","KOA Speer Electronics, Inc."
"R28","1","13k","","","","Resistor_SMD:R_0805_2012Metric","RK73H2ATTD1302F","KOA Speer Electronics, Inc."
"R26,R27,R50,R53,R54,R55,R56","7","1k","","","","Resistor_SMD:R_0805_2012Metric","RC0805FR-131KL ","YAGEO "
"SchmittDis1,schmittEN1","2","0","","","","Resistor_SMD:R_0603_1608Metric","RK73Z1JTTD","KOA Speer Electronics, Inc."
"R22","1","120K","","","","Resistor_SMD:R_0603_1608Metric","RK73H1JTTD1203F","KOA Speer Electronics, Inc."
"R18,R19,R20,R21,R24,R25","6","20k","","","","Resistor_SMD:R_0603_1608Metric","RK73H1JTTD2002F","KOA Speer Electronics, Inc."
"R8,R9,R10,R11,R13,R14,R15,R16","8","10K","","","","Resistor_SMD:R_0603_1608Metric","RK73H1JTTD1002F","KOA Speer Electronics, Inc."
"R4,R6,R7,R12,R17","5","10k","","","","Resistor_SMD:R_0603_1608Metric","RK73H1JTTD1002F","KOA Speer Electronics, Inc."
"R3,R5,R23","3","1k","","","","Resistor_SMD:R_0603_1608Metric","RK73H1JTTD1001F","KOA Speer Electronics, Inc."
"R1,R2","2","500k","","","","Resistor_SMD:R_0603_1608Metric","RT0603BRC07500RL","KOA Speer Electronics, Inc."
"VR1,VR2,VR3,VR4","4","3296Y-11-103LF","","","","Potentiometer_THT:Potentiometer_Bourns_3296Y_Vertical","3296Y-1-103LF","Bourns"
"Q1,Q2,Q3,Q4","4","IRLIZ44N NMOS","","","","Package_TO_SOT_THT:TO-220F-3_Vertical","IRLIZ44NPBF","Infineon Technologies"
"Q5,Q6,Q7","3","PMOS IRF9540","","","","Package_TO_SOT_THT:TO-220F-3_Horizontal_TabDown","IRF9540PBF","Vishay Siliconix"
"U3","1","LT1084-5.0","","","","Package_TO_SOT_THT:TO-220-3_Horizontal_TabDown","LT1084CT-5#PBF","Analog Devices "
"U4,U5,U7","3","LM393","","","","Package_DIP:DIP-8_W7.62mm_Socket","LM393N","Texas Instruments"
"U8","1","LM555xN","","","","Package_DIP:DIP-8_W7.62mm","LM555CN/NOPB","Texas Instruments"
"U6","1","CD4071BE OR Gate","","","","Package_DIP:DIP-14_W7.62mm_Socket","CD4071BE","Texas Instruments"
"U2","1","4081 AND Gate","","","","Package_DIP:DIP-14_W7.62mm_Socket","CD4081BE","Texas Instruments"
"U1","1","40106 Inverter","","","","Package_DIP:DIP-14_W7.62mm_Socket","CD40106BE","Texas Instruments"
"H5,H6,H7,H8","4","MountingHole","","Excluded from BOM","","MountingHole:MountingHole_3.2mm_M3","",""
"H1,H2,H3,H4","4","MH","","","","MountingHole:MountingHole_3mm","",""
"D6,D8,D11","3","DEBUG LED","","","","LED_THT:LED_D5.0mm","WP7113ID","Kingbright"
"D4","1","ON when ok","","","","LED_THT:LED_D5.0mm","WP7113ID","Kingbright"
"BothThreshold1,brkErr1,OutOfRange1","3","APTD2012LSYCK","","","","LED_SMD:LED_0805_2012Metric_Pad1.15x1.40mm_HandSolder","APTD2012LSYCK","Kingbright"
"J11","1","Dash","","","","footprints:Molex_Mini-Fit_Jr_5566-06A_2x03_P4.20mm_Vertical","0039281083","Molex"
"K1,K2,K3","3","G6B-2214P-US DC12","","","","footprints:DPSTrelay","G6B-2214P-US-DC12","Omron Electronics "
"J19","1","AMP","","","","footprints:AmpBoard","",""
"U9","1","OKX-T/5-D12N-C","","","","footprints:12v5vDCDC","OKX-T/5-D12N-C","Murata Power Solutions"
"J13","1","614004135023","","","","footprints:614004135023","614004135023","Wurth Elektronik"
"J18","1","39306207","","","","footprints:20pSTminfit","39306207","Molex"
"J14","1","footwell","","","","footprints:14pSTminifit","0039281143","Molex "
"J17","1","SHOCK/WHEEL SNSR","","","","footprints:12pSTminifit","39-30-6127","Molex"
"J12","1","BBC","","","","footprints:12pSTminifit","39-30-6127","Molex"
"D1,D2,D3,D5,D7,D9,D10,D12","8","D","","","","Diode_SMD:D_0603_1608Metric","1N4148W-7-F","Diodes Incorporated "
"PS1","1","I7A24080A033V-0C3-R","","","","DCDCfootprints:24V DCDC I7A24080A033V0C3R","I7A24080A033V-0C3-R","TDK-Lambda"
"C16,C21,C25,C29","4","330uF","","","","Capacitor_SMD:C_2220_5750Metric_Pad1.97x5.40mm_HandSolder","16SVPK330M","Panasonic Electronic Components"
"C31,C32,C33,C34","4","100n","","","","Capacitor_SMD:C_0805_2012Metric","CC0805KRX7R9BB104 ","YAGEO"
"C26","1","10nF","","","","Capacitor_SMD:C_0805_2012Metric","CL21B103KBANNNC ","Samsung Electro-Mechanics"
"C24","1","10uF","","","","Capacitor_SMD:C_0805_2012Metric","EMK212BJ106KG-T ","Taiyo Yuden "
"C17,C22,C23,C28","4","22uF","","","","Capacitor_SMD:C_0805_2012Metric","GRM21BR61A226ME44L","Murata"
"C12,C13","2","100nF","","","","Capacitor_SMD:C_0805_2012Metric","GRM21BR71H104KA01L","Murata"
"C11,C14,C15,C18,C19,C20,C27,C30","8","1uF","","","","Capacitor_SMD:C_0805_2012Metric","CL21B105KBFNNNE ,GRM21BR71H105KA12L","Murata,Samsung Electro-Mechanics"
"C5,C6,C7,C8,C9,C10","6","0.1uF","","","","Capacitor_SMD:C_0603_1608Metric","GRM188R71H104KA93D","Murata"
"C4","1","3.3uF","","","","Capacitor_SMD:C_0603_1608Metric","CL10A335KP8NNNC","Samsung"
"C2,C3","2","1nF","","","","Capacitor_SMD:C_0603_1608Metric","GRM188R71H102KA01D","Murata"
"C1","1","10uF","","","","Capacitor_SMD:C_0603_1608Metric","GRM188R60J106ME47D","Murata"
"SW1,SW2,SW3","3","SW_Push","","","","Button_Switch_THT:SW_PUSH_6mm","B3F-1000","Omron Electronics"
"J10","1","TSSI","","","","0footprints:Molex_Mini-Fit_Jr_5566-04A_2x02_P4.20mm_Vertical","0039288040","Molex"
"J9","1","Current Sensor","","","","0footprints:Molex_Mini-Fit_Jr_5566-04A_2x02_P4.20mm_Vertical","0039288040","Molex"
"J4","1","ACCU","","","","0footprints:Molex_Mini-Fit_Jr_5566-04A_2x02_P4.20mm_Vertical","0039288040","Molex"
"J16","1","Brakelight","","","","0footprints:Molex_Mini-Fit_Jr_5566-02A_2x01_P4.20mm_Vertical","0039310028","Molex"
"J15","1","RTD B","","","","0footprints:Molex_Mini-Fit_Jr_5566-02A_2x01_P4.20mm_Vertical","0039310028","Molex"
"J8","1","5v EXP","","","","0footprints:Molex_Mini-Fit_Jr_5566-02A_2x01_P4.20mm_Vertical","0039310028","Molex"
"J7","1","24v EXP","","","","0footprints:Molex_Mini-Fit_Jr_5566-02A_2x01_P4.20mm_Vertical","0039310028","Molex"
"J6","1","PWR IN","","","","0footprints:Molex_Mini-Fit_Jr_5566-02A_2x01_P4.20mm_Vertical","0039310028","Molex"
"J5","1","12v EXP","","","","0footprints:Molex_Mini-Fit_Jr_5566-02A_2x01_P4.20mm_Vertical","0039310028","Molex"
"J3","1","SDC OUT","","","","0footprints:Molex_Mini-Fit_Jr_5566-02A_2x01_P4.20mm_Vertical","0039310028","Molex"
"J2","1","TS ON SW","","","","0footprints:Molex_Mini-Fit_Jr_5566-02A_2x01_P4.20mm_Vertical","0039310028","Molex"
"J1","1","Estop","","","","0footprints:Molex_Mini-Fit_Jr_5566-02A_2x01_P4.20mm_Vertical","0039310028","Molex"
"F12","1","~","","","","0footprints:FUSE_3522-2","01530007Z","Littelfuse"
"F11","1","3A","","","","0footprints:FUSE_3522-2","01530007Z","Littelfuse"
"F4,F8,F9","3","10A MAX","","","","0footprints:FUSE_3522-2","01530007Z","Littelfuse"
"F2,F3,F6,F7,F10","5","5A MAX","","","","0footprints:FUSE_3522-2","01530007Z","Littelfuse"
"F1,F5","2","2A MAX","","","","0footprints:FUSE_3522-2","01530007Z","Littelfuse"
